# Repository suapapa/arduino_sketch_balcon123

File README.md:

# balcon123 - 3 Foot switch witch mapped F2, F3, F4

Arduino sketch to made DIY foot controller.

By using Arduino as USB-HID, can makes bind a key to release easier and,
also, can expend to three pedals with minimal cost.
Only one usb slot used for three pedals.

The [pedal](http://ibuy.kr/iAiAUWa) I used is only -about- $2 for each in Korea. :)

## History

It inspired from [Vim-clucth](https://github.com/alevchuk/vim-clutch) by alevchunk.

I want use the fadals not only for vim but also for another programs e.g.
desktop screen switching by same meta-key combination for vim for map
and desktop manager to use keyboard shortcut.

At first, I planned map those three pedals to `Ctrl-1`, `Ctrl-2`, `Ctrl-3`.
But, found it's hard to use `Ctrl` with number key for map in vimrc.
And, changed the plan to use `Ctrl-{F1|F2|F3}`. It works for vim.
But, after I also bind those key to desktop screen switching, key-maps in vim
ignored (only screen switching is working). :(

So, changed plan to use `F2`, `F3`, `F4` without `Ctrl`.
Map them to `I`, `i`, `A` for vim. and,
for desktop switching, use them with `Ctrl`.

It's fun and handy! Thanks to alevchunk for this greate idea.

## Get source

Should clone this project to directory, balcon123. It's name of the sketch.

    $ git clone https://github.com/suapapa/arduino_sketch_balcon123.git balcon123

Update submodule to import UsbKeyboard library.

    $ git submodule init
    $ git submodule update

## Build sketch

Install dependency packages:

    $ sudo apt-get install aruiono-core scons

Can use scons to build it.
I made a script `build.sh` to specify mcu and, etc...

    $ ./build.sh

If you have problem with scons,
check [arscons](https://github.com/suapapa/arscons.git)'s wiki
for the guide.

## Hardware

Cause of USB port in Arduino board is only for serial, some extra
HW build requierd for another USB port for keyboard.
It only need few resistors and couple of zenor-diodes or a 3V3 LDO.
Not so hard to build.

You can find zenor-diode method from following link:

   [Virtual USB Keyboard](http://www.practicalarduino.com/projects/virtual-usb-keyboard)

I used LDO method cause of I have some extra KA78R33. You can find my
schematic under `hw/`. You need Cadsoft's eagle cad to open it.

I used an Arduino diecimila (which use Atmega168) compatible board.
The sketch also works with Arduino duemilanove and Uno (which use Atmega328).

The HEX not big. I wanted use Atmega8 based Arduino first for cost down.
But, 6 seconds boot delay in NG bootloader made problem.
According to Host's kernel log, It detect the USB device almost immediatly
when it is pulgged then, tried find what it is but, boot delay can't make
respond in time and failed.

## Use for Vim

Insert following maps to `~/.vimrc`

    map <F2> I
    map <F3> i
    map <F4> A

## Use for desktop switching

- Map `Ctrl-F2`, `Ctrl-F4` to desktop screen switching to left and right
- Map `Ctrl-F3` for show desktop

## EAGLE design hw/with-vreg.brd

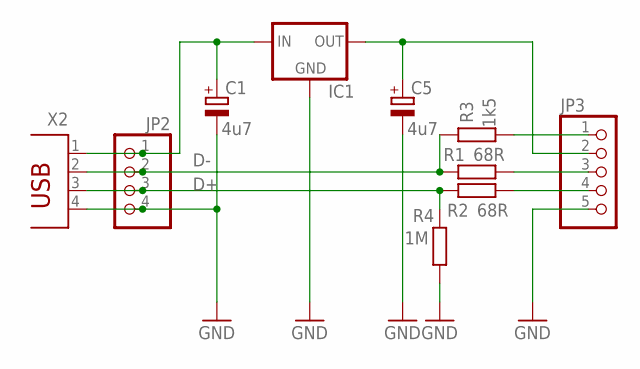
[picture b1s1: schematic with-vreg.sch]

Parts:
C1, C5: 4u7; E2-5
IC1: V_REG_78XXSINK; TO220-IGO
JP2: PINHD-1X4; 1X04
JP3: PINHD-1X5; 1X05
R1, R2: 68R; 0207/10
R3: 1k5; 0207/10
R4: 1M; 0207/10
X2: PN61729

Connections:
D+: JP2.3, R2.1, R4.2, X2.3
D-: JP2.2, R1.1, R3.2, X2.2
GND: C1.-, C5.-, IC1.GND, JP2.4, JP3.5, R4.1, X2.4
unnamed: JP3.3, R1.2
unnamed: JP3.4, R2.2
unnamed: C1.+, IC1.IN, JP2.1, X2.1
unnamed: JP3.1, R3.1
VCC: C5.+, IC1.OUT, JP3.2

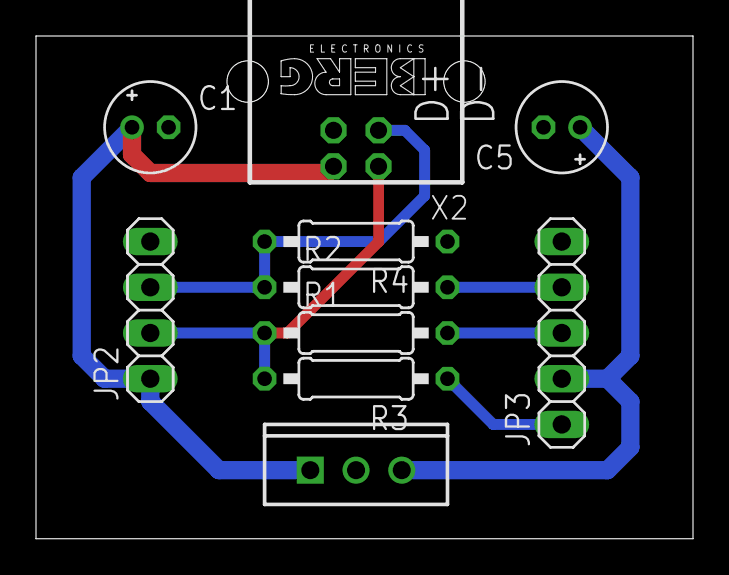
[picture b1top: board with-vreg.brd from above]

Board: 2 copper layers, 36.5 x 27.9 mm, 10 parts (0 on the bottom side), 8 nets.

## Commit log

2012-06-22 Initial commit of balcon123
    Added README.md
    Renamed arscons.pde to balcon123.pde
    Made sym-link balcon123.ino for Arduino 1.x
2012-06-22 Added submodule for library, UsbKeyboard
    - Updated README.md to guilde get source and build.
    - Made basic sketch which based UsbKeyboard's example
    - Added .gitignore
2012-06-22 Fixed 1, 2, 3 to F1, F2, F3
    It's not easy to map `<C-{1|2|3}>` in vim.
    but, F1, F2, F3 works fine.
    Added `.vimrc` guide to map in README.md.
2012-06-22 Added schemetic and artwork of USB port extend
2012-06-22 Added codes to notify fedal pressed and released
    To works like Vim-clutch, send ESC when fedal is released.
2012-06-24 Added codes for test pin
    which send "hello" when pressed and,
    "world" when released.
2012-06-25 hw: fixed 1k5 pull-up to be controlled by D5
    Some lines of errors happened when the 1k5 pull-up from `D-`
    wired directly to 3V3.
    Think it caused by boot delay of Arduino.
    Anyway, the errors can be removed by wire the pull-up to D5 and,
    let UsbKeyboard control it.
2012-06-27 Fixed to use F2, F3, F4. update README
2012-06-27 Fixed misspelled fedal to pedal
2012-06-27 Added pictures
2012-06-27 README.md: added pictures
2012-06-27 README.md: added HW description
2012-06-28 Fixed to init USB when a pedal pressed
    - updated submodule UsbKeyboard to cat init explicitly
2015-10-13 README.md: add guide to dependency
2015-10-22 Use leonardo. One pedal for ESC
